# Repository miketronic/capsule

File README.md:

# capsule
Capsule keyboard design

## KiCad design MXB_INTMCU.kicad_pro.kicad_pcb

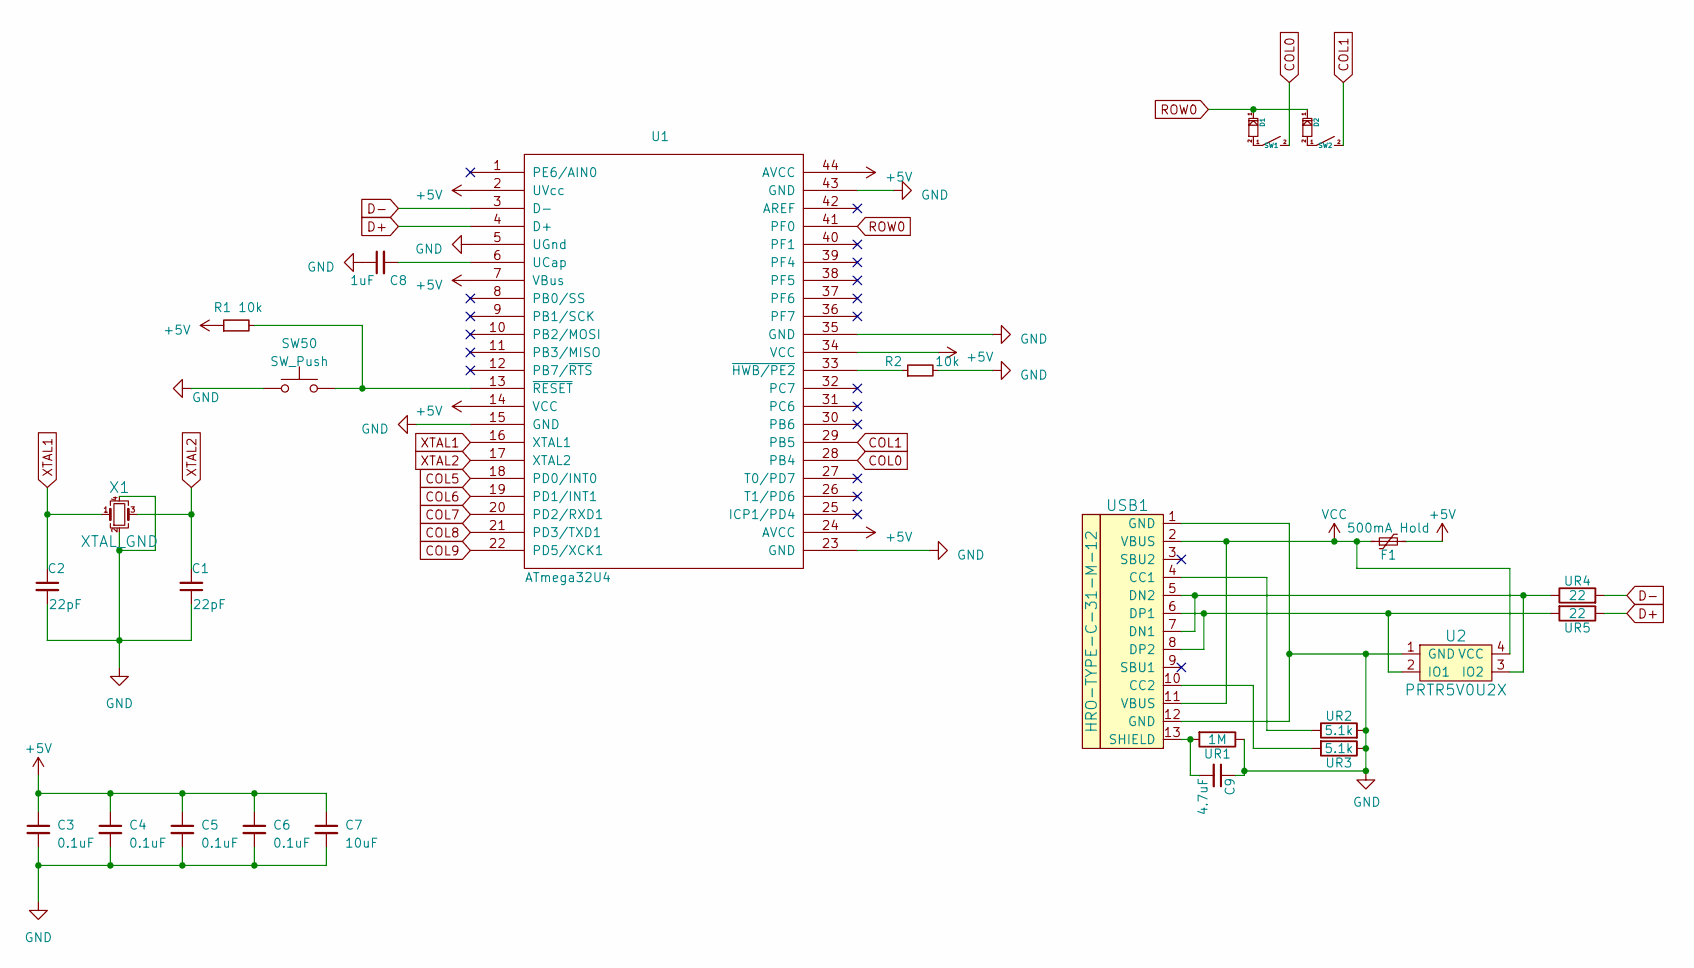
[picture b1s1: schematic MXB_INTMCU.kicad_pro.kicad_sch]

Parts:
C1, C2: 22pF; C_0805_2012Metric
C3, C4, C5, C6: 0.1uF; C_0805_2012Metric
C7: 10uF; C_0805_2012Metric
C8: 1uF; C_0805_2012Metric
C9: 4.7uF; C_0805_2012Metric
D1, D2: D; Diode-Hybrid-Back
F1: 500mA Hold; Fuse_1206_3216Metric
R1, R2: 10k; R_0805_2012Metric
SW1, SW2: SW; MB_KailhChoc-1U_17mm
SW50: SW_Push; SKQG-1155865
U1: ATmega32U4; TQFP-44_10x10mm_P0.8mm
U2: PRTR5V0U2X; SOT-143B
UR1: 1M; R_0805
UR2, UR3: 5.1k; R_0805
UR4, UR5: 22; R_0805
USB1: HRO-TYPE-C-31-M-12; HRO-TYPE-C-31-M-12-Assembly
X1: XTAL_GND; Crystal_SMD_SeikoEpson_FA238-4Pin_3.2x2.5mm

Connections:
+5V: C3.1, C4.1, C5.1, C6.1, C7.1, F1.2, R1.1, U1.2 (UVcc), U1.7 (VBus), U1.14 (VCC), U1.24 (AVCC), U1.34 (VCC), U1.44 (AVCC)
COL0: SW1.2, U1.28 (PB4)
COL1: SW2.2, U1.29 (PB5)
COL5: U1.18 (PD0/INT0)
COL6: U1.19 (PD1/INT1)
COL7: U1.20 (PD2/RXD1)
COL8: U1.21 (PD3/TXD1)
COL9: U1.22 (PD5/XCK1)
D+: U1.4 (D+), UR5.1
D-: U1.3 (D-), UR4.2
GND: C1.1, C2.2, C3.2, C4.2, C5.2, C6.2, C7.2, C8.1, C9.1, R2.2, SW50.1, U1.5 (UGnd), U1.15 (GND), U1.23 (GND), U1.35 (GND), U1.43 (GND), U2.1 (GND), UR1.1, UR2.2, UR3.1, USB1.1 (GND), USB1.12 (GND), X1.2, X1.4
unnamed: D1.2, SW1.1
unnamed: D2.2, SW2.1
unnamed: C8.2, U1.6 (UCap)
unnamed: R2.1, U1.33 (~HWB/PE2)
unnamed: R1.2, SW50.2, U1.13 (~RESET)
unnamed: U2.2 (IO1), UR5.2, USB1.6 (DP1), USB1.8 (DP2)
unnamed: U2.3 (IO2), UR4.1, USB1.5 (DN2), USB1.7 (DN1)
unnamed: UR2.1, USB1.4 (CC1)
unnamed: UR3.2, USB1.10 (CC2)
unnamed: C9.2, UR1.2, USB1.13 (SHIELD)
ROW0: D1.1, D2.1, U1.41 (PF0)
VCC: F1.1, U2.4 (VCC), USB1.2 (VBUS), USB1.11 (VBUS)
XTAL1: C2.1, U1.16 (XTAL1), X1.1
XTAL2: C1.2, U1.17 (XTAL2), X1.3

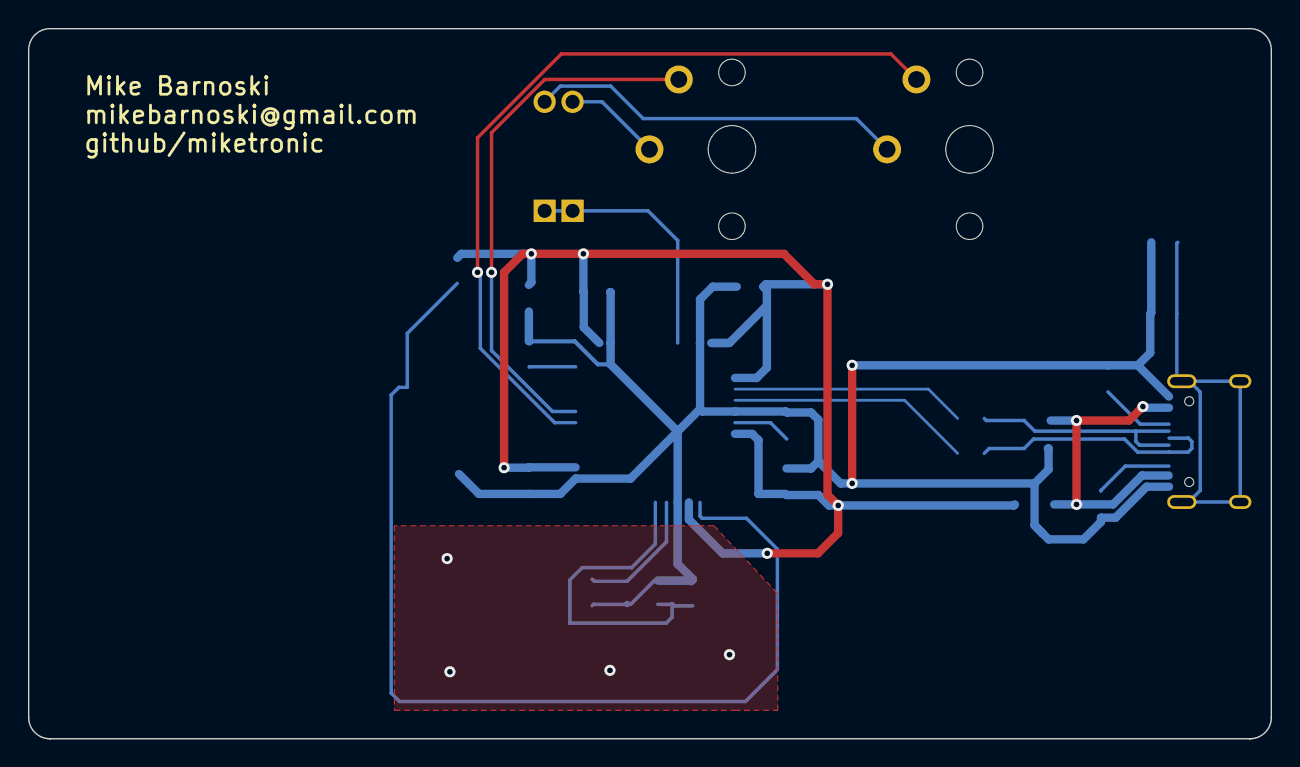
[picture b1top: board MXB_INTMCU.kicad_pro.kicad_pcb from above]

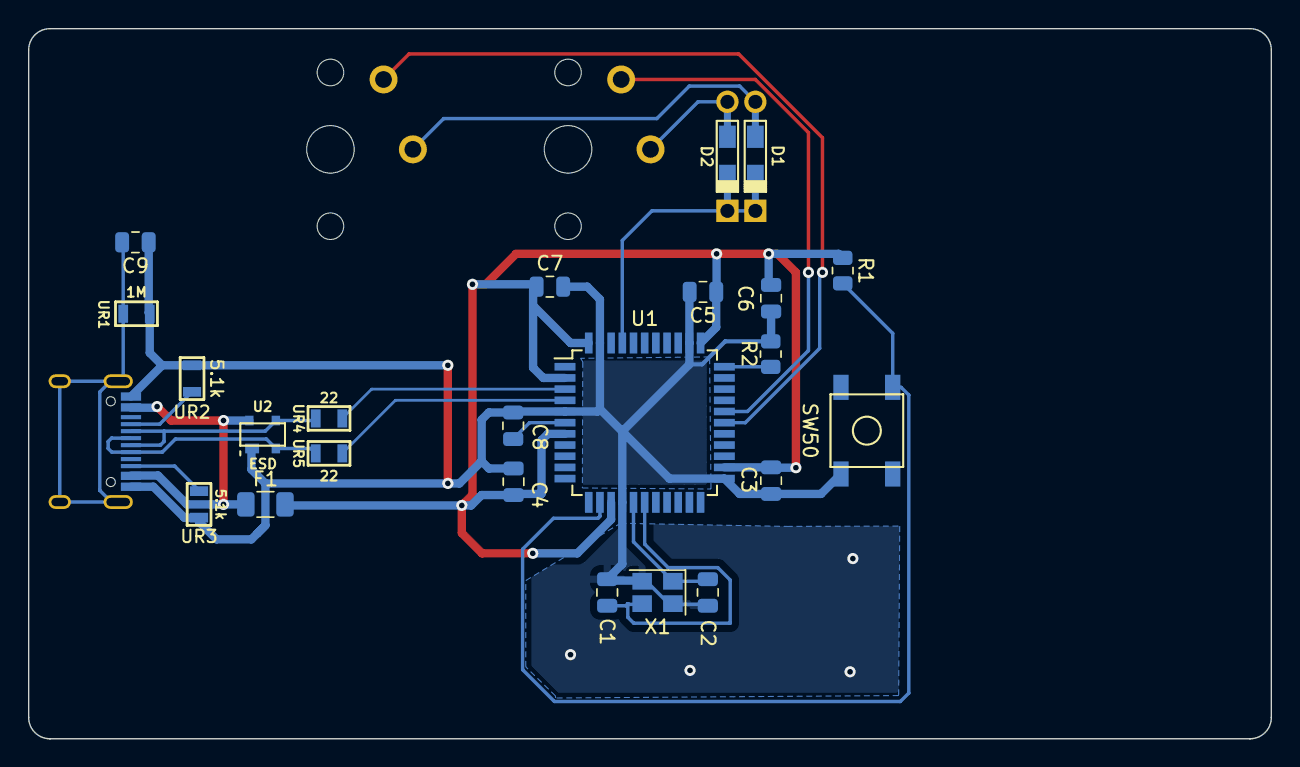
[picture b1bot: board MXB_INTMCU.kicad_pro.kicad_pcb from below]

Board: 2 copper layers, 88.9 x 50.8 mm, 26 parts (22 on the bottom side), 20 nets.

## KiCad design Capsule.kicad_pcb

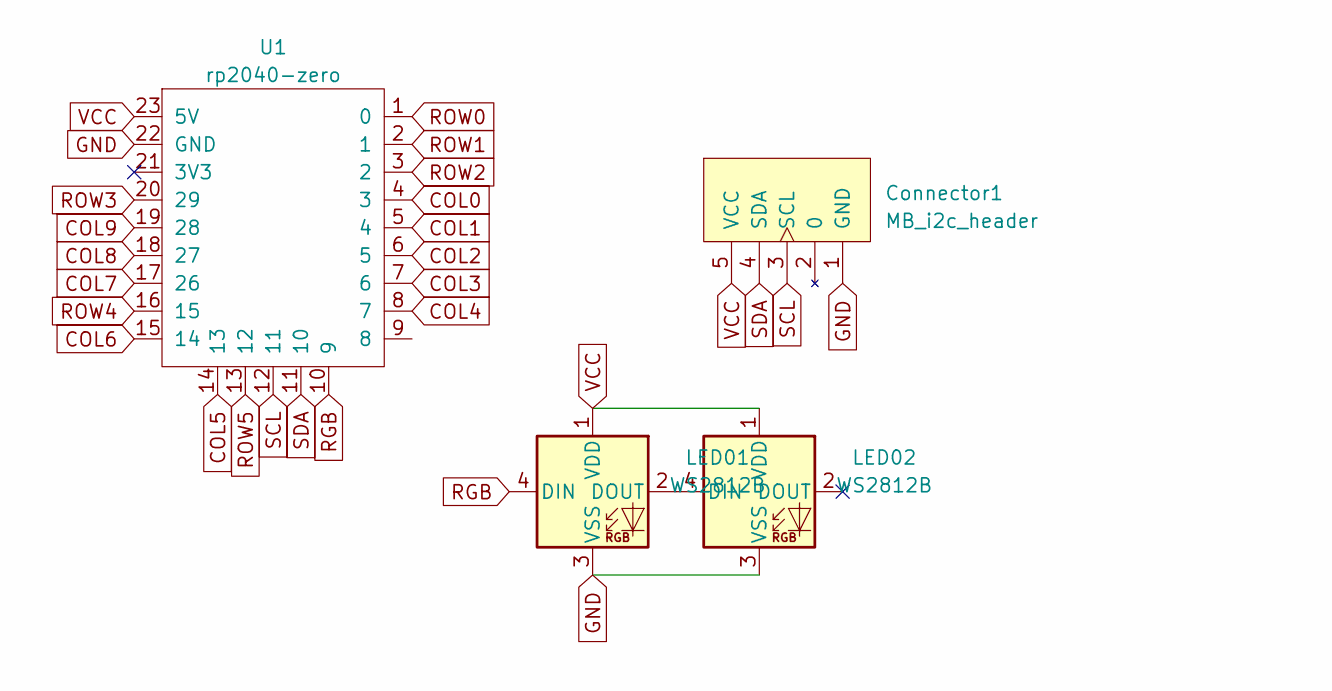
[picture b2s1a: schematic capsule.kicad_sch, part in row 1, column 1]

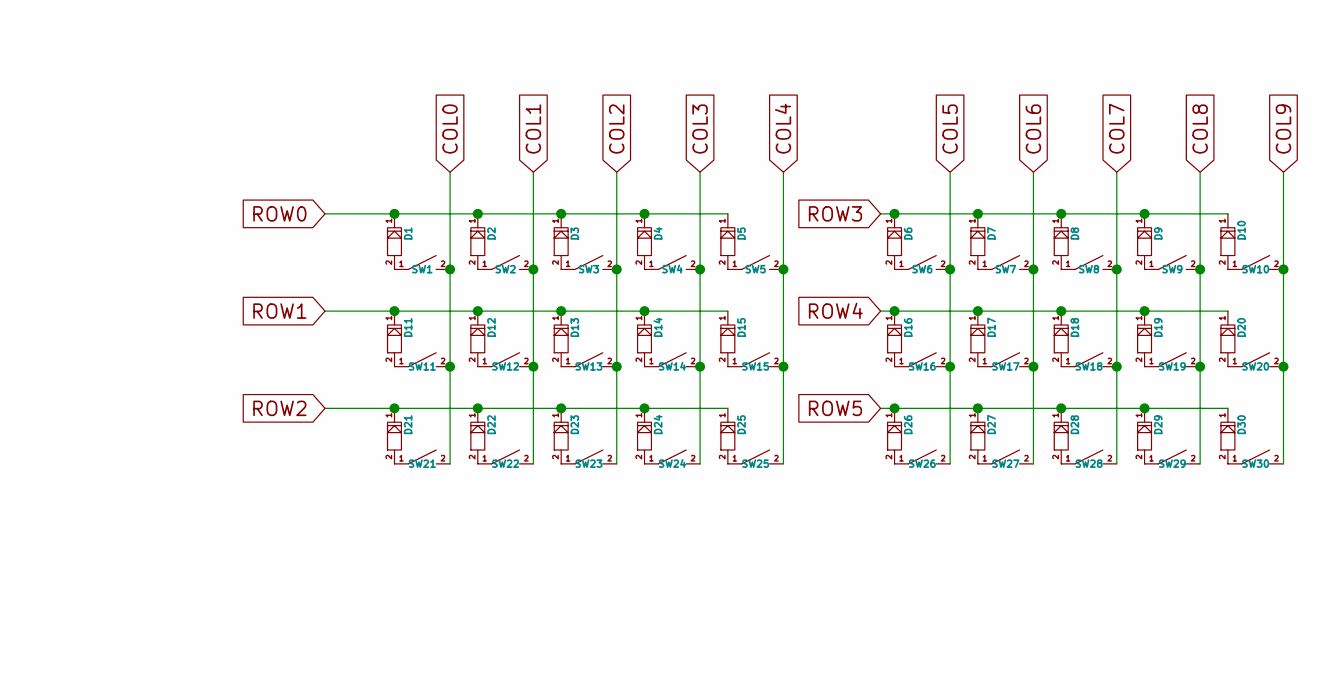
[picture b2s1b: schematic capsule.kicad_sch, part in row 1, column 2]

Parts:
Connector1: MB_i2c_header; MB_I2C_Breakout_reverse
D1, D2, D3, D4, D5, D6, D7, D8, D9, D10, D11, D12, D13, D14, D15, D16, D17, D18, D19, D20, D21, D22, D23, D24, D25, D26, D27, D28, D29, D30: D; MB_D_SOD-123_1PAD
LED01, LED02: WS2812B; LED_WS2812B_PLCC4_5.0x5.0mm_P3.2mm
SW1, SW2, SW3, SW4, SW5, SW6, SW7, SW8, SW9, SW10, SW11, SW12, SW13, SW14, SW15, SW16, SW17, SW18, SW19, SW20, SW21, SW22, SW23, SW24, SW25, SW26, SW27, SW28, SW29, SW30: SW; MB_KailhChoc-1U_17mm
U1: rp2040-zero; MB_rp2040-zero-tht

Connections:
COL0: SW1.2, SW11.2, SW21.2, U1.4 (3)
COL1: SW2.2, SW12.2, SW22.2, U1.5 (4)
COL2: SW3.2, SW13.2, SW23.2, U1.6 (5)
COL3: SW4.2, SW14.2, SW24.2, U1.7 (6)
COL4: SW5.2, SW15.2, SW25.2, U1.8 (7)
COL5: SW6.2, SW16.2, SW26.2, U1.14 (13)
COL6: SW7.2, SW17.2, SW27.2, U1.15 (14)
COL7: SW8.2, SW18.2, SW28.2, U1.17 (26)
COL8: SW9.2, SW19.2, SW29.2, U1.18 (27)
COL9: SW10.2, SW20.2, SW30.2, U1.19 (28)
GND: Connector1.1 (GND), LED01.3 (VSS), LED02.3 (VSS), U1.22 (GND)
unnamed: D1.2, SW1.1
unnamed: D2.2, SW2.1
unnamed: D3.2, SW3.1
unnamed: D4.2, SW4.1
unnamed: D5.2, SW5.1
unnamed: D6.2, SW6.1
unnamed: D7.2, SW7.1
unnamed: D8.2, SW8.1
unnamed: D9.2, SW9.1
unnamed: D10.2, SW10.1
unnamed: D11.2, SW11.1
unnamed: D12.2, SW12.1
unnamed: D13.2, SW13.1
unnamed: D14.2, SW14.1
unnamed: D15.2, SW15.1
unnamed: D16.2, SW16.1
unnamed: D17.2, SW17.1
unnamed: D18.2, SW18.1
unnamed: D19.2, SW19.1
unnamed: D20.2, SW20.1
unnamed: D21.2, SW21.1
unnamed: D22.2, SW22.1
unnamed: D23.2, SW23.1
unnamed: D24.2, SW24.1
unnamed: D25.2, SW25.1
unnamed: D26.2, SW26.1
unnamed: D27.2, SW27.1
unnamed: D28.2, SW28.1
unnamed: D29.2, SW29.1
unnamed: D30.2, SW30.1
unnamed: LED01.2 (DOUT), LED02.4 (DIN)
RGB: LED01.4 (DIN), U1.10 (9)
ROW0: D1.1, D2.1, D3.1, D4.1, D5.1, U1.1 (0)
ROW1: D11.1, D12.1, D13.1, D14.1, D15.1, U1.2 (1)
ROW2: D21.1, D22.1, D23.1, D24.1, D25.1, U1.3 (2)
ROW3: D6.1, D7.1, D8.1, D9.1, D10.1, U1.20 (29)
ROW4: D16.1, D17.1, D18.1, D19.1, D20.1, U1.16 (15)
ROW5: D26.1, D27.1, D28.1, D29.1, D30.1, U1.13 (12)
SCL: Connector1.3 (SCL), U1.12 (11)
SDA: Connector1.4 (SDA), U1.11 (10)
VCC: Connector1.5 (VCC), LED01.1 (VDD), LED02.1 (VDD), U1.23 (5V)

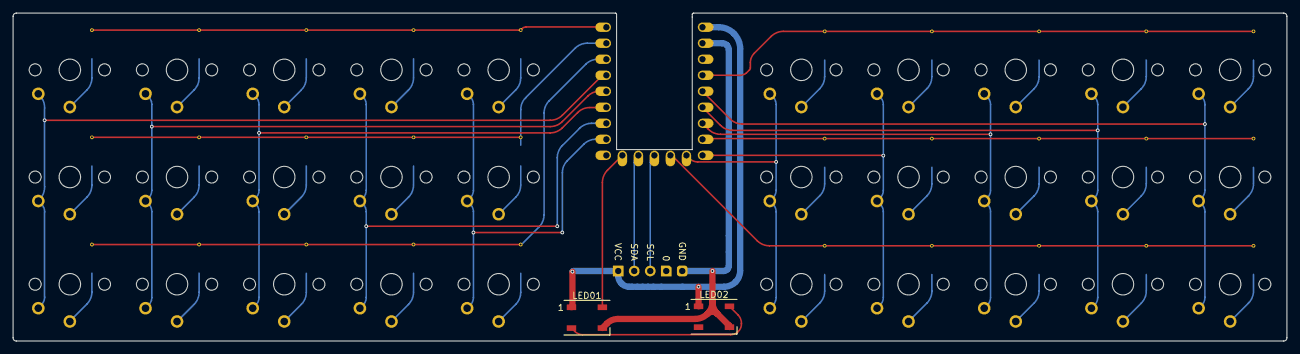
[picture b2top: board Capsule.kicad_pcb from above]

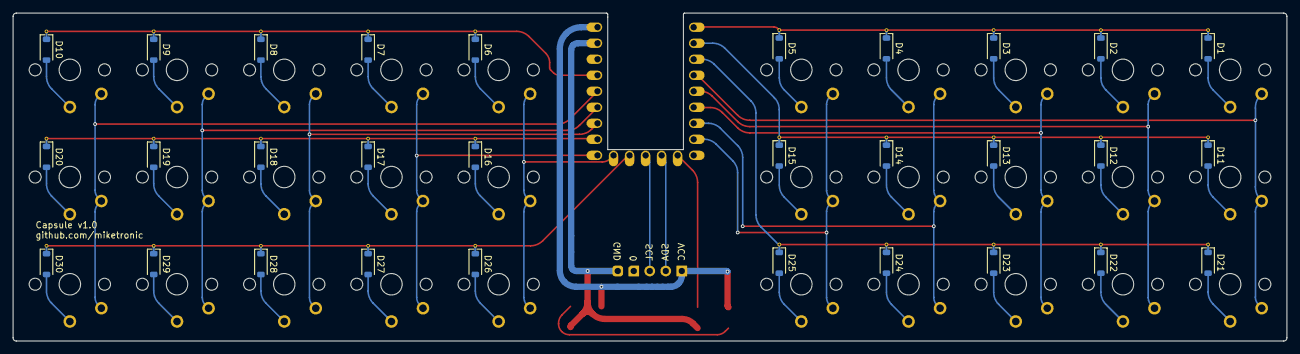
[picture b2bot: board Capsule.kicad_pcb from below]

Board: 2 copper layers, 202.0 x 52.0 mm, 64 parts (31 on the bottom side), 52 nets.

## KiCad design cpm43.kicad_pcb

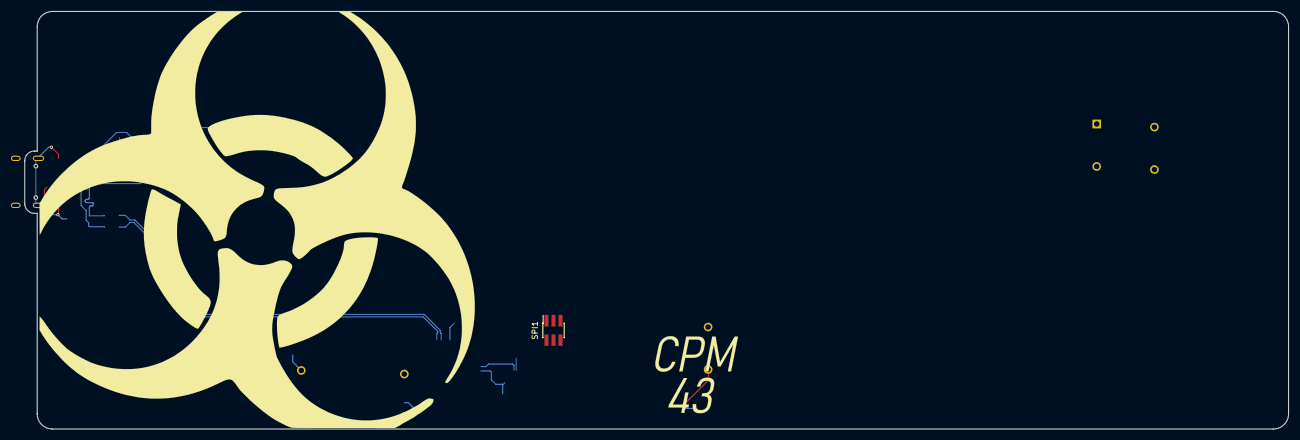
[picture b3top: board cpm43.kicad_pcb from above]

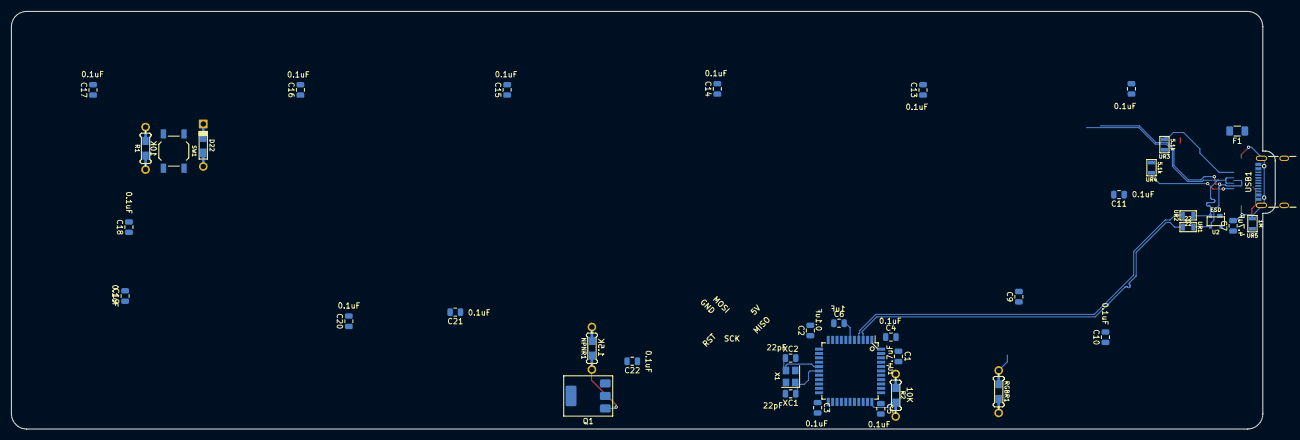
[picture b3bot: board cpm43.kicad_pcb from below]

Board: 2 copper layers, 232.2 x 76.7 mm, 41 parts (35 on the bottom side), 20 nets.

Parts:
C1: 0.1uf; C_0805_2012Metric
C2, C3, C5, C9, C10, C11, C12, C13, C14, C15, C16, C17, C18, C19, C20, C21, C22: 0.1uF; C_0805_2012Metric
C4, C7: 4.7uF; C_0805_2012Metric
C6: 1uF; C_0805_2012Metric
D22: D; Diode-Hybrid-Back
F1: 500mA Hold; Fuse_1206_3216Metric
NPNR1: 1.5k; Resistor-Hybrid-Back
Q1: Q_NPN_BCE; SOT-223-3_TabPin2
R1, R2: 10k; Resistor-Hybrid-Back
RGBR1: 470; Resistor-Hybrid-Back
SPI1: 2x3 SPI; PinSocket_2x03_P1.27mm_Vertical_SMD
SW1: SW_PUSH; SW_SPST_TL3342
U1: ATmega32U4; TQFP-44_10x10mm_Pitch0.8mm
U2: PRTR5V0U2X; SOT-143B
UR1, UR2: 22; R_0805
UR3, UR4: 5.1k; R_0805
UR5: 1M; R_0805
USB1: HRO-TYPE-C-31-M-12; USB_C_Receptacle_GCT_USB4105-xx-A_16P_TopMnt_Horizontal
X1: Crystal_GND24; Crystal_SMD_3225-4pin_3.2x2.5mm
XC1, XC2: 22pF; C_0805_2012Metric

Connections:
+5V: C1.1, C2.1, C3.1, C4.1, C5.1, C9.1, C10.1, C11.1, C12.1, C13.1, C14.1, C15.1, C16.1, C17.1, C18.1, C19.1, C20.1, C21.1, C22.1, F1.2, R1.1, SPI1.2, U1.2 (UVCC), U1.7 (VBUS), U1.14 (VCC), U1.24 (AVCC), U1.34 (VCC), U1.44 (AVCC)
D+: U1.4 (D+), UR2.1
D-: U1.3 (D-), UR1.2
GND: C1.2, C2.2, C3.2, C4.2, C5.2, C6.1, C7.1, C9.2, C10.2, C11.2, C12.2, C13.2, C14.2, C15.2, C16.2, C17.2, C18.2, C19.2, C20.2, C21.2, C22.2, Q1.3 (E), R2.2, SPI1.6, SW1.1, U1.5 (UGND), U1.15 (GND), U1.23 (GND), U1.35 (GND), U1.43 (GND), U2.1 (GND), UR3.1, UR4.2, UR5.1, X1.2, X1.4, XC1.2, XC2.2
LEDPWM: NPNR1.1, U1.29 ((ADC12/OC1A/~OC4B/PCINT12)PB5)
MISO: SPI1.1, U1.11 ((PDO/MISO/PCINT3)PB3)
MOSI: SPI1.4, U1.10 ((PDI/MOSI/PCINT2)PB2)
unnamed: U2.3 (IO2), UR1.1
unnamed: U2.2 (IO1), UR2.2
unnamed: NPNR1.2, Q1.1 (B)
unnamed: R2.1, U1.33 ((~HWB)PE2)
unnamed: C6.2, U1.6 (UCAP)
unnamed: U1.17 (XTAL1), X1.1, XC1.1
unnamed: U1.16 (XTAL2), X1.3, XC2.1
unnamed: C7.2, UR5.2
RGBIN: RGBR1.1, U1.30 ((ADC13/OC1B/OC4B/PCINT13)PB6)
ROW1: D22.1, U1.31 ((OC3A/~OC4A)PC6)
RST: R1.2, SPI1.5, SW1.2, U1.13 (RESET)
SCK: SPI1.3, U1.9 ((SCLK/PCINT1)PB1)
VCC: F1.1, U2.4 (VCC)

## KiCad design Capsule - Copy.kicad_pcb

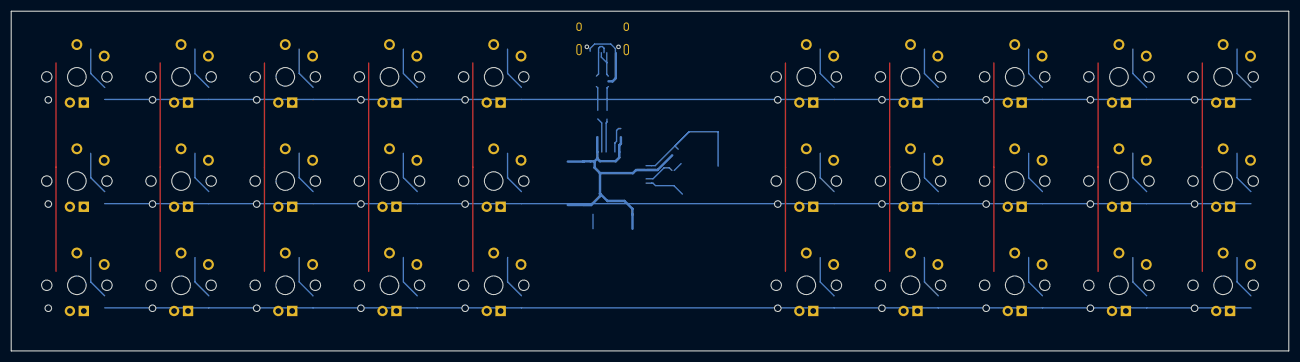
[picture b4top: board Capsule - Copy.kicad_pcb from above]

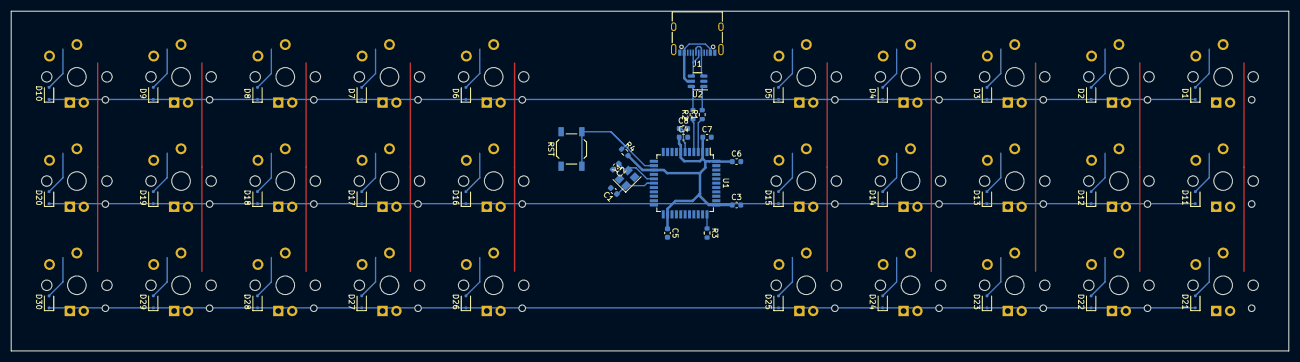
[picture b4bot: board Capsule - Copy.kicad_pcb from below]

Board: 2 copper layers, 233.5 x 62.1 mm, 77 parts (47 on the bottom side), 56 nets.

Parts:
C1, C2: 22p; C_0603_1608Metric
C3, C4, C5, C6: 0.1u; C_0603_1608Metric
C7: 4.7u; C_0603_1608Metric
C8: 1u; C_0603_1608Metric
D1, D2, D3, D4, D5, D6, D7, D8, D9, D10, D11, D12, D13, D14, D15, D16, D17, D18, D19, D20, D21, D22, D23, D24, D25, D26, D27, D28, D29, D30: D; D_SOD-323F
J1: USB_C_Receptacle_USB2.0; USB_C_Receptacle_XKB_U262-16XN-4BVC11
R1, R2: 22; R_0603_1608Metric
R3, R4: 10k; R_0603_1608Metric
RST: SW_SPST; SW_SPST_TL3342
SW1, SW2, SW3, SW4, SW5, SW6, SW7, SW8, SW9, SW10, SW11, SW12, SW13, SW14, SW15, SW16, SW17, SW18, SW19, SW20, SW21, SW22, SW23, SW24, SW25, SW26, SW27, SW28, SW29, SW30: SW_Push; KailhChoc-1U
U1: ATmega32U4-A; TQFP-44_10x10mm_P0.8mm
U2: TPD2S017; SOT-23-6
Y1: Crystal_GND24; Crystal_SMD_3225-4Pin_3.2x2.5mm

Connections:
COL0: SW1.1, SW11.1, SW21.1, U1.11
COL1: SW2.1, SW12.1, SW22.1, U1.28
COL2: SW3.1, SW13.1, SW23.1, U1.29
COL3: SW4.1, SW14.1, SW24.1, U1.30
COL4: SW5.1, SW15.1, SW25.1, U1.12
COL7: SW6.1, SW16.1, SW26.1, U1.31
COL8: SW7.1, SW17.1, SW27.1, U1.32
COL9: SW8.1, SW18.1, SW28.1, U1.18
COL10: SW9.1, SW19.1, SW29.1, U1.19
COL11: SW10.1, SW20.1, SW30.1, U1.20
GND: C1.2, C2.2, C3.2, C4.2, C5.2, C6.2, C7.2, C8.2, J1.A1, J1.A12, J1.B1, J1.B12, J1.S1, R3.2, RST.1, U1.5, U1.15, U1.23, U1.35, U1.43, U2.2, Y1.2, Y1.4
unnamed: D1.2, SW1.2
unnamed: D2.2, SW2.2
unnamed: D3.2, SW3.2
unnamed: D4.2, SW4.2
unnamed: D5.2, SW5.2
unnamed: D6.2, SW6.2
unnamed: D7.2, SW7.2
unnamed: D8.2, SW8.2
unnamed: D9.2, SW9.2
unnamed: D10.2, SW10.2
unnamed: D11.2, SW11.2
unnamed: D12.2, SW12.2
unnamed: D13.2, SW13.2
unnamed: D14.2, SW14.2
unnamed: D15.2, SW15.2
unnamed: D16.2, SW16.2
unnamed: D17.2, SW17.2
unnamed: D18.2, SW18.2
unnamed: D19.2, SW19.2
unnamed: D20.2, SW20.2
unnamed: D21.2, SW21.2
unnamed: D22.2, SW22.2
unnamed: D23.2, SW23.2
unnamed: D24.2, SW24.2
unnamed: D25.2, SW25.2
unnamed: D26.2, SW26.2
unnamed: D27.2, SW27.2
unnamed: D28.2, SW28.2
unnamed: D29.2, SW29.2
unnamed: D30.2, SW30.2
ROW0: D1.1, D2.1, D3.1, D4.1, D5.1, D6.1, D7.1, D8.1, D9.1, D10.1, U1.8
ROW1: D11.1, D12.1, D13.1, D14.1, D15.1, D16.1, D17.1, D18.1, D19.1, D20.1, U1.9
ROW2: D21.1, D22.1, D23.1, D24.1, D25.1, D26.1, D27.1, D28.1, D29.1, D30.1, U1.10
VCC: C3.1, C4.1, C5.1, C6.1, C7.1, J1.A4, J1.A9, J1.B4, J1.B9, R4.2, U1.2, U1.7, U1.14, U1.24, U1.34, U1.44, U2.5
mcu/D+: R2.1, U1.4
mcu/D-: R1.1, U1.3
mcu/UCAP: C8.1, U1.6
mcu/XTAL1: C1.1, U1.17, Y1.1
mcu/XTAL2: C2.1, U1.16, Y1.3
mcu/~HWB/PE2: R3.1, U1.33
mcu/~RESET: R4.1, RST.2, U1.13
u2/D+: R2.2, U2.6
u2/D-: R1.2, U2.1
usb/D+: J1.A6, J1.B6, U2.4
usb/D-: J1.A7, J1.B7, U2.3

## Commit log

2023-06-09 Initialize project
2023-06-09 add submodules
2023-06-09 Add footprint libraries
2023-06-09 SCH refactor
2023-06-09 pcb update
2023-06-12 pcb refactor
2023-06-21 big update
